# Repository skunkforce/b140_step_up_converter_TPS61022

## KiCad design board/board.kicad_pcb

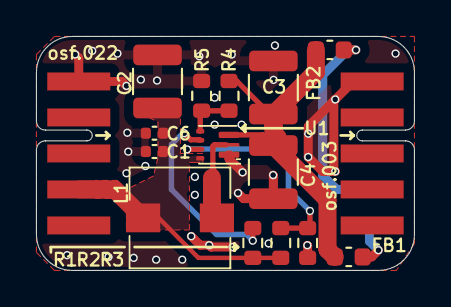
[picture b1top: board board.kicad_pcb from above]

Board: 4 copper layers, 21.0 x 13.0 mm, 17 parts (1 on the bottom side), 9 nets.

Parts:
C1: 1uF; C_0402_1005Metric
C2: 10uF; C_1210_3225Metric
C3, C4: 33uF; C_1210_3225Metric
C6: 100nF; C_0402_1005Metric
FB1, FB2: 200R, 5A; C_0603_1608Metric
J1: 022_battery_cells; on_edge_2x05_device
J2: 003_power; on_edge_2x05_host
L1: 744316100
LOGO1: Logo_Open_Hardware_Small; OSHW-Symbol_6.7x6mm_SilkScreen
R1, R2, R3: 10k; R_0603_1608Metric
R4: 732k; R_0603_1608Metric
R5: 100k; R_0603_1608Metric
U1: TPS61022

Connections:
/implementation/EN: R1.2, U1.5 (EN)
/implementation/FB: R4.2, R5.1, U1.4 (FB)
/implementation/MODE: R2.2, R3.1, U1.6 (MODE)
/implementation/SW: L1.2, U1.2 (SW)
/implementation/VIN: C1.1, C2.1, C6.1, J1.4 (C2+C3-), L1.1, R1.1, R2.1, U1.7 (VIN)
/implementation/VOUT: C3.1, C4.1, FB1.1, FB2.1, R4.1, U1.3 (VOUT)
GND: C1.2, C2.2, C3.2, C4.2, C6.2, J1.1 (GND), J2.1 (GND), R3.2, R5.2, U1.1 (GND)
unnamed: FB2.2, J2.9 (3.3V)
unnamed: FB1.2, J2.10 (5V)

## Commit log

2023-07-01 reduced ground pins to be compatable with more connector types
